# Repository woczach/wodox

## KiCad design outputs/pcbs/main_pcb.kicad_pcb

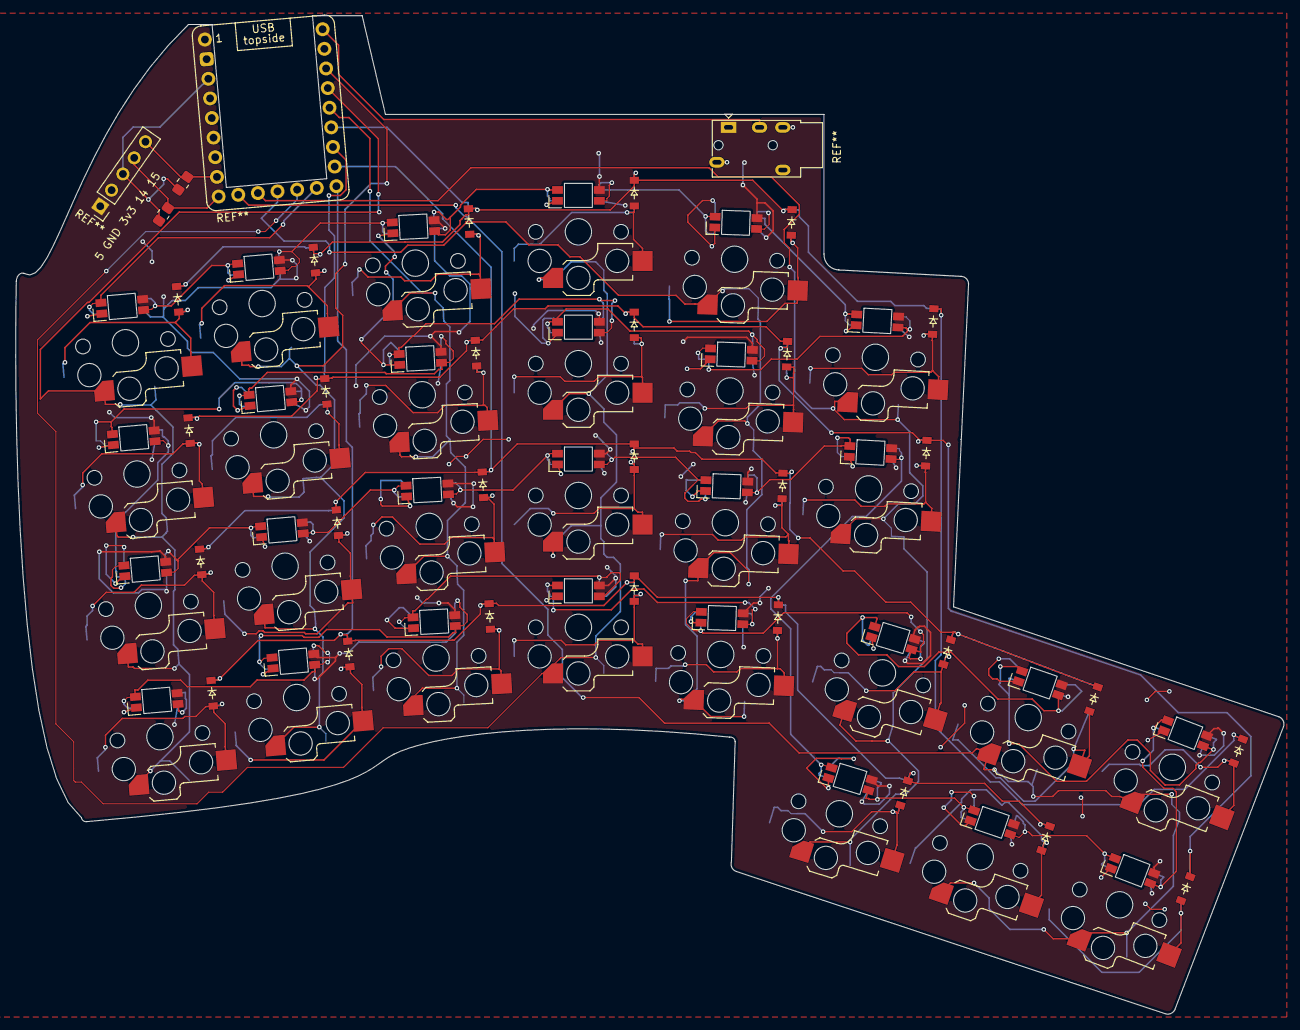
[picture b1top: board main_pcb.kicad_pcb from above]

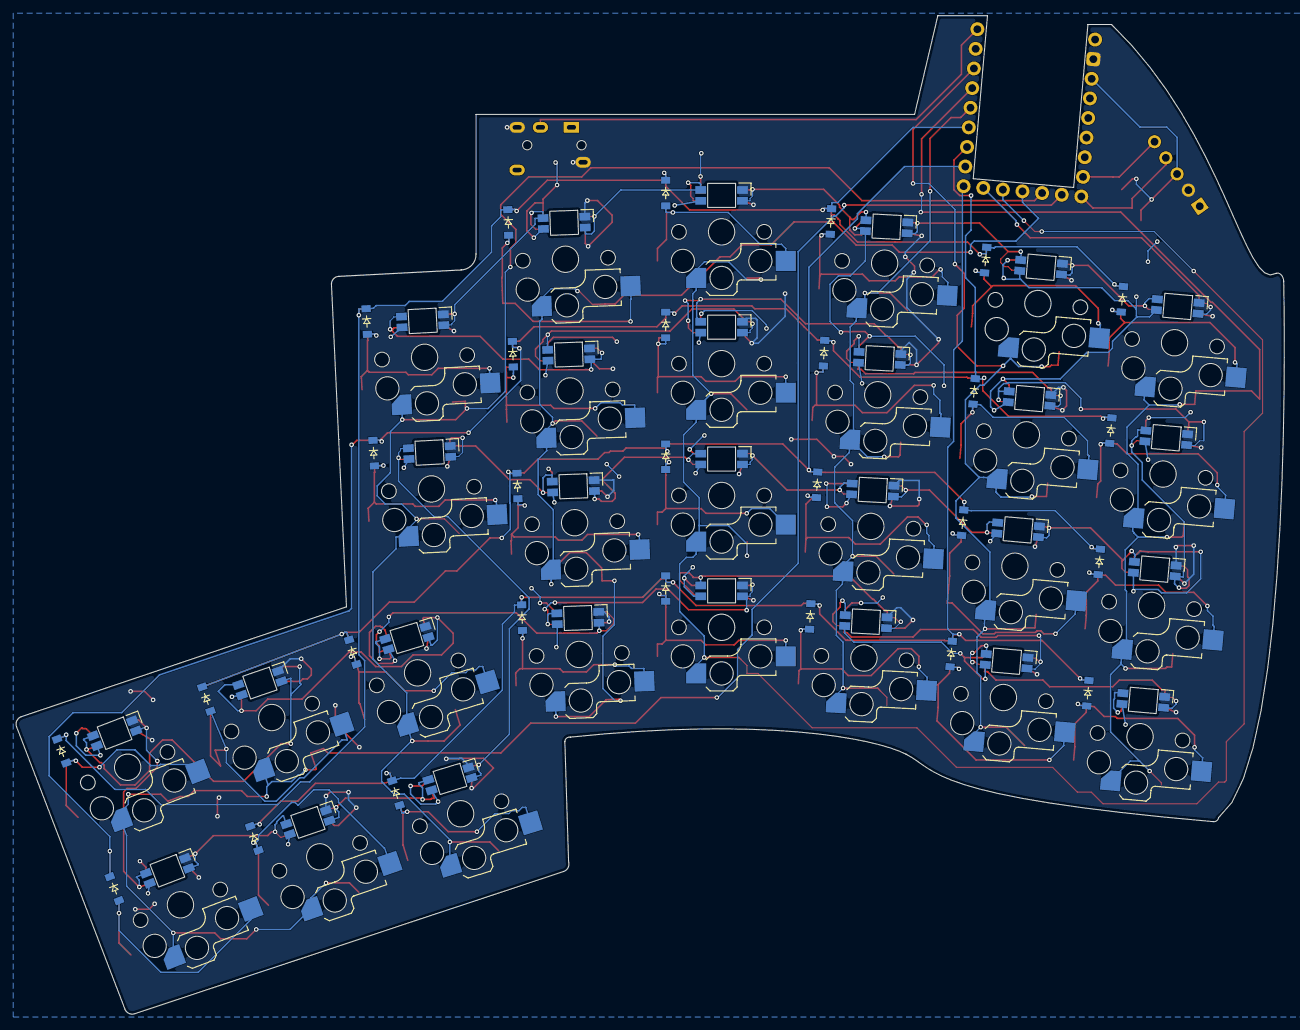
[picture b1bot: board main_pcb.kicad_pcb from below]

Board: 2 copper layers, 163.5 x 128.8 mm, 84 parts (28 on the bottom side), 68 nets.

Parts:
D1, D2, D3, D4, D5, D6, D7, D8, D9, D10, D11, D12, D13, D14, D15, D16, D17, D18, D19, D20, D21, D22, D23, D24, D25, D26, D27, D28: diode_tht_sod123
LED1, LED2, LED3, LED4, LED5, LED6, LED7, LED8, LED9, LED10, LED11, LED12, LED13, LED14, LED15, LED16, LED17, LED18, LED19, LED20, LED21, LED22, LED23, LED24, LED25, LED26, LED27, LED28: led_SK6812mini-e (per-key, reversible)
S1, S2, S3, S4, S5, S6, S7, S8, S9, S10, S11, S12, S13, S14, S15, S16, S17, S18, S19, S20, S21, S22, S23, S24, S25, S26, S27, S28: switch_choc_v1_v2

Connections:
D1: LED4.2, LED8.4
D2: LED8.2, LED12.4
D3: LED12.2, LED16.4
D4: LED16.2, LED20.4
D5: LED20.2, LED22.4
D6: LED19.4, LED22.2
D7: LED15.4, LED19.2
D8: LED11.4, LED15.2
D9: LED7.4, LED11.2
D10: LED3.4, LED7.2
D11: LED2.4, LED3.2
D12: LED2.2, LED6.4
D13: LED6.2, LED10.4
D14: LED10.2, LED14.4
D15: LED14.2, LED18.4
D16: LED18.2, LED21.4
D17: LED21.2, LED23.4
D18: LED23.2, LED25.4
D19: LED25.2, LED27.4
D20: LED27.2, LED28.4
D21: LED26.4, LED28.2
D22: LED24.4, LED26.2
D23: LED17.4, LED24.2
D24: LED13.4, LED17.2
D25: LED9.4, LED13.2
D26: LED5.4, LED9.2
D27: LED1.4, LED5.2
GND: LED1.3, LED2.3, LED3.3, LED4.3, LED5.3, LED6.3, LED7.3, LED8.3, LED9.3, LED10.3, LED11.3, LED12.3, LED13.3, LED14.3, LED15.3, LED16.3, LED17.3, LED18.3, LED19.3, LED20.3, LED21.3, LED22.3, LED23.3, LED24.3, LED25.3, LED26.3, LED27.3, LED28.3
K_0: S1.1, S2.1, S3.1, S4.1
K_1: S5.1, S6.1, S7.1, S8.1
K_2: S9.1, S10.1, S11.1, S12.1
K_3: S13.1, S14.1, S15.1, S16.1
K_4: S17.1, S18.1, S19.1, S20.1
K_5: S21.1, S22.1, S23.1, S24.1
R_0: D4.1, D8.1, D12.1, D16.1, D20.1, D22.1, D28.1
R_1: D3.1, D7.1, D11.1, D15.1, D19.1, D21.1, D27.1
R_2: D2.1, D6.1, D10.1, D14.1, D18.1, D24.1, D26.1
R_3: D1.1, D5.1, D9.1, D13.1, D17.1, D23.1, D25.1
VCC: LED1.1, LED2.1, LED3.1, LED4.1, LED5.1, LED6.1, LED7.1, LED8.1, LED9.1, LED10.1, LED11.1, LED12.1, LED13.1, LED14.1, LED15.1, LED16.1, LED17.1, LED18.1, LED19.1, LED20.1, LED21.1, LED22.1, LED23.1, LED24.1, LED25.1, LED26.1, LED27.1, LED28.1
k_0_r_0: D4.2, S4.2
k_0_r_1: D3.2, S3.2
k_0_r_2: D2.2, S2.2
k_0_r_3: D1.2, S1.2
k_1_r_0: D8.2, S8.2
k_1_r_1: D7.2, S7.2
k_1_r_2: D6.2, S6.2
k_1_r_3: D5.2, S5.2
k_2_r_0: D12.2, S12.2
k_2_r_1: D11.2, S11.2
k_2_r_2: D10.2, S10.2
k_2_r_3: D9.2, S9.2
k_3_r_0: D16.2, S16.2
k_3_r_1: D15.2, S15.2
k_3_r_2: D14.2, S14.2
k_3_r_3: D13.2, S13.2
k_4_r_0: D20.2, S20.2
k_4_r_1: D19.2, S19.2
k_4_r_2: D18.2, S18.2
k_4_r_3: D17.2, S17.2
k_5_r_1: D22.2, S22.2
k_5_r_2: D21.2, S21.2
t1_td: D23.2, S23.2
t1_tu: D24.2, S24.2
t2_td: D25.2, S25.2
t2_tu: D26.2, S26.2
t3_td: D27.2, S27.2
t3_tu: D28.2, S28.2
t_2: S25.1, S26.1, S27.1, S28.1
